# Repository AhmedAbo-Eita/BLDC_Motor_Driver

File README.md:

# 3-Phase BLDC & PMSM Motor Controller (ESC)

[-blue)](https://www.st.com/en/microcontrollers-microprocessors/stm32g431rb.html)

A high-performance, compact 3-phase Field-Oriented Control (FOC) Brushless DC (BLDC) and Permanent Magnet Synchronous Motor (PMSM) driver designed for robotics, e-mobility, actuators, and industrial automation.

This repository contains the complete end-to-end design stack:
* **Hardware:** Production-ready 8-layer PCB design (KiCad 10), complete multi-sheet schematics, BOM, Gerbers, assembly files, and LTspice circuit simulations.
* **Firmware:** Embedded C project for STM32G431 utilizing hardware CORDIC/FMAC acceleration, advanced motor timers, ADCs, and industrial communication stacks.
* **Control Modeling:** MATLAB/Simulink system-level simulation models for FOC algorithm development, parameter tuning, and sensorless state estimation.

---

## Hardware Preview (BLDC_MC_V1.0)

---

## Hardware V1.0 Summary & Highlight

### Key Technical Specifications

| Parameter | Specification | Details / Subsystem |
| :--- | :--- | :--- |
| **Operating Voltage ($V_{BUS}$)** | **24 V – 60 V** (60 V max) | Active reverse-polarity protection + TVS transient clamping |
| **Rated Phase Current** | **30 A continuous / peak** | Low $R_{DS(on)}$ MOSFETs + 8-layer high-copper thermal dissipation |
| **PWM Switching Frequency** | Up to **100 kHz** | Driven by STM32 advanced motor control timers |
| **Microcontroller** | **STM32G431RBT6** | 170 MHz ARM Cortex-M4, FPU, CORDIC & FMAC co-processors |
| **Gate Driver IC** | **TI DRV8353HRTAR** | Smart gate driver ($1.4\,\text{A}$ source / $700\,\text{mA}$ sink), $V_{DS}$ monitor |
| **Power Inverter Stage** | 6x **Infineon BSC027N10NS5** | 100 V, $2.7\,\text{m}\Omega$, SuperSO-8 (TDSON-8) with RC snubbers |
| **Current Sensing** | 3x **$1\,\text{m}\Omega$ Shunts** | Low-side 3-shunt sensing with shielded 4-wire Kelvin routing |
| **Voltage / BEMF Sensing** | 3-Phase Resistor Dividers | Buffered with active $+1.65\,\text{V}$ virtual ground (TLV9061) |
| **Position Feedback** | Hall Sensors + Encoders | Buffered 5 V to 3.3 V Hall inputs with RC filtering |
| **Onboard Memory** | **256 Kbit SPI EEPROM** | Microchip 25LC256 for calibration parameters & PID profiles |
| **Connectivity** | **CAN / CAN-FD, USB-C, UART, I2C** | TCAN334DR transceiver + USBLC6-2SC6 ESD protection |
| **Auxiliary Power Supplies** | **12 V / 5 V / 3.3 V** | LM74700 Ideal Diode, 12V Buck, NCV4274 (5V), LDL1117 (3.3V) |
| **PCB Form Factor** | **8-Layer High-TG180 FR4** | 2 oz outer copper, controlled impedance, 1.65 mm thickness |

---

## Repository Structure

```text
BLDC_Motor_Driver/
├── Control_Modeling/       # MATLAB & Simulink models for FOC algorithm simulation
├── Firmware/               # STM32G431 embedded C firmware (STM32CubeIDE)
└── Hardware/               # Hardware designs, simulations & manufacturing files
    ├── BLDC_MC_V1.0/       # KiCad design, schematics, BOM, Gerbers & 3D renders
    └── Simulation/         # LTspice circuit simulations
```

---

## Project Development Status

| Subsystem | Milestone | Status | Details |
| :--- | :--- | :---: | :--- |
| **Hardware (V1.0)** | Schematic & PCB Layout | **Completed** | 10 modular schematic sheets, DRC passed, 8-layer stackup |
| **Hardware (V1.0)** | Fabrication Files (Gerbers/BOM/PnP) | **Completed** | Full manufacturing package generated in [`Output_Job_files`](Hardware/BLDC_MC_V1.0/Output_Job_files/) |
| **Hardware (V1.0)** | Circuit Simulations | **Completed** | Hall sensor conditioning and active virtual-ground voltage sensor validated |
| **Firmware** | BSP & Low-level Drivers | **In Progress** | STM32G431 peripheral configuration (PWM timers, ADCs, SPI, CAN, UART) |
| **Firmware** | FOC & Commutation Algorithms | **In Progress** | Space Vector PWM (SVPWM), Park/Clarke transforms, current control loop |
| **Control Modeling** | System-Level Simulation | **In Progress** | Simulink motor and inverter models for tuning PI loops & observing dynamics |

---

## Detailed Hardware Documentation & Deliverables

For full details on the schematic sheet breakdown, connector pinouts, controlled impedance layout rules, and fabrication deliverables, refer to:
* **[Hardware V1.0 Comprehensive Documentation](Hardware/BLDC_MC_V1.0/Readme.md)**
* **[Hardware Versions & Overview](Hardware/Readme.md)**
* **[Schematic PDF](Hardware/BLDC_MC_V1.0/Output_Job_files/Board_SCH/BLDC_MC_V1.0.pdf)**
* **[Bill of Materials (BOM)](Hardware/BLDC_MC_V1.0/Output_Job_files/BOM_File/BLDC_MC_V1.0_PDF.pdf)**
* **[Fabrication Gerber Files](Hardware/BLDC_MC_V1.0/Output_Job_files/Fabrication_Files/)**

---

## Author & Project Information

* **Lead Hardware Engineer:** Ahmed Aboeita
* **Design Tools:** KiCad 10.0.5, STM32CubeIDE, MATLAB / Simulink, LTspice

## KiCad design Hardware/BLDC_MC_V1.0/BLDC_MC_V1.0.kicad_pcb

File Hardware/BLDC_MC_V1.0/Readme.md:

# 60V / 30A High-Performance BLDC & PMSM Motor Controller (ESC)

A compact, high-efficiency, 3-phase Field-Oriented Control (FOC) motor controller designed for high-power robotics, e-mobility, and industrial automation. Built on the **STM32G431RBT6** ARM Cortex-M4 MCU and the **TI DRV8353HRTAR** smart gate driver, this board supports high-frequency switching up to 100 kHz with extensive hardware protection, sensor feedback, and connectivity.

---

## Technical Specifications

| Parameter | Specification | Notes / Details |
| :--- | :--- | :--- |
| **Input DC Bus Voltage ($V_{BUS}$)** | **24V – 60V** (**60V Maximum**) | High-voltage bulk capacitor bank + TVS clamping |
| **Maximum Phase Current** | **30A Maximum** | Dependent on external heatsinking and thermal interface |
| **Maximum Switching Frequency** | Up to **100 kHz PWM** | Hardware-accelerated CORDIC/FMAC trigonometric engine |
| **Operating Temperature ($T_A$)** | **$-40^\circ\text{C}$ to $+125^\circ\text{C}$** | Designed for High-TG180 PCB substrates |
| **Main Processing Unit** | **STM32G431RBT6** (170 MHz) | ARM Cortex-M4 with FPU, 128KB Flash, 32KB SRAM |
| **Gate Driver IC** | **TI DRV8353HRTAR** | Smart Gate Drive ($1.4\text{A}$ source / $700\text{mA}$ sink) |
| **Power MOSFETs** | 6x **Infineon BSC027N10NS5** | 100V, $2.7\text{ m}\Omega$, SuperSO-8 (TDSON-8) |
| **Current Sense Shunts** | 3x **$1\text{ m}\Omega$ Metal Plate** | Low-side 3-shunt topology with Kelvin Sensing |
| **PCB Form Factor / Layers** | **8-Layer High-TG180 FR4** | 2 oz outer copper / 1 oz inner planes |

---

## Key Hardware Features

### 1. Processing & Control Core
* **STM32G431RBT6 MCU:** High-performance motor control MCU with integrated CORDIC co-processor for near-zero latency Park/Clarke transformations.
* **Dual Clock Source:** 24 MHz primary oscillator (`Y1`) for the main system PLL and 32.768 kHz crystal (`Y2`) for precise real-time timing.
* **Onboard Memory:** 256 Kbit SPI EEPROM (**25LC256-E/SN**) for non-volatile calibration parameters, PID coefficients, and motor profiles.

### 2. Inverter Power Stage & Gate Drive
* **Smart Gate Driver (DRV8353H):** Eliminates external gate resistors via software-tunable `IDRIVE` configuration. Features integrated $V_{DS}$ monitoring for cross-conduction and shoot-through protection.
* **Optimized Power Stage:** Low $R_{DS(on)}$ ($2.7\text{ m}\Omega$) 100V OptiMOS 5 MOSFETs paired with localized **1 nF + 4.7 $\Omega$ switch-node RC snubbers** to eliminate high-frequency parasitic ringing.
* **DC-Link Decoupling:** Low-ESR parallel ceramic capacitor bank ($4\times 47\,\mu\text{F} + 2\times 100\text{ nF}$) placed immediately across the inverter bridge for fast switching transient absorption.

### 3. Sensing & Signal Conditioning
* **3-Phase Low-Side Current Sensing:** $1\text{ m}\Omega$ shunts routed via strict 4-wire Kelvin differential pairs directly into the DRV8353 current sense amplifiers.
* **Phase Voltage / Sensorless BEMF Sensing:** Three buffered resistor divider networks ($100\text{ k}\Omega / 2.7\text{ k}\Omega$) with an active **+1.65V Virtual Ground buffer (TLV9061)** to allow full bidirectional phase voltage sampling across the MCU's ADC dynamic range.
* **Sensored Hall Interface:** Isolated Hall-effect inputs with hardware low-pass filtering and **TLV9061** op-amp buffers shifting 5V Hall signals safely to 3.125V/3.3V logic levels.

### 4. Auxiliary Power Architecture
* **Active Reverse Polarity Protection:** High-side Ideal Diode controller (**TI LM74700-Q1**) driving a power MOSFET to block reverse connection with zero diode forward-voltage drops.
* **Step-Down Buck Converter:** Converts high-voltage DC input down to an intermediate **+12V rail** for gate drive supplies.
* **Dual Linear Regulators (LDOs):**
  * **NCV4274 (5.0V):** Powers external Hall sensors and peripheral pull-ups.
  * **LDL1117S33R (3.3V):** Ultra-clean, low-noise supply for the STM32G4 MCU, analog references, and transceivers.

### 5. Robust Industrial Connectivity & Protection
* **CAN / CAN-FD Bus:** High-speed **TCAN334DR** transceiver with an **ACT1210** common-mode choke, split $60\Omega$ termination, and dedicated **PESD2CANFD24V-QCZ** ESD diode protection.
* **USB Type-C Interface:** USB 2.0 Type-C port with **USBLC6-2SC6** high-speed TVS diode array for diagnostics, firmware flashing, and PC telemetry.
* **Series Damping Resistors:** $33\,\Omega$ series termination resistors placed on all high-speed digital lines (PWM, SPI, SWD, UART, I2C) to ensure signal integrity and eliminate trace reflections.

---

## Schematic Sheet Architecture

The schematic is organized into 10 modular hierarchical sheets:

| Sheet ID | Sheet Name | Description & Subsystems |
| :---: | :--- | :--- |
| **01/10** | `BLDC_MC.kicad_sch` | Top-level hierarchical block interconnections and system bus mapping. |
| **02/10** | `BLDC_MC_V1.0_Power.kicad_sch` | LM74700 Ideal Diode, 12V Buck regulator, 5V/3.3V LDOs, status LEDs. |
| **03/10** | `BLDC_MC_V1.0_MCU.kicad_sch` | STM32G431RBT6, decoupling network, SWD debug port, USB-C interface. |
| **04/10** | `BLDC_MC_V1.0_Gate_Drive.kicad_sch` | DRV8353HRTAR smart gate driver, IDRIVE, VDS, and shunt amplifier tuning. |
| **05/10** | `BLDC_MC_V1.0_3Phase_Inverter_legs.kicad_sch` | 3-Phase MOSFET half-bridges, RC snubbers, $1\text{ m}\Omega$ current shunts. |
| **06/10** | `BLDC_MC_V1.0_HallSensor.kicad_sch` | 3-Channel Hall-effect sensor level-shifter and TLV9061 buffer circuitry. |
| **07/10** | `BLDC_MC_V1.0_Voltage_Sensor.kicad_sch` | 3-Phase BEMF divider network and +1.65V active virtual ground op-amp. |
| **08/10** | `BLDC_MC_V1.0_Memory.kicad_sch` | 25LC256 256Kbit SPI EEPROM and line termination resistors. |
| **09/10** | `BLDC_MC_V1.0_CAN_Transceiver.kicad_sch` | TCAN334DR CAN/CAN-FD transceiver, split termination, common-mode filter. |
| **10/10** | `BLDC_MC_V1.0_Connectors.kicad_sch` | High-current power pads, J8 comms header, J5 Hall header, TVS arrays. |

---

## Connector Pinout Definitions

### 1. Main Power & Motor Terminals (High Current)
* **`J6 / J9`:** DC Bus Input Power (`Vin_DC` [+] and `PGND` [-]).
* **`J1`:** Motor Phase A Output (`Phase_A`).
* **`J2`:** Motor Phase B Output (`Phase_B`).
* **`J7`:** Motor Phase C Output (`Phase_C`).

### 2. Communication Header (`J8` - 10-Pin S10B-PHDSS)
| Pin # | Net Name | Type | Description |
| :---: | :--- | :---: | :--- |
| **1** | `+3.3V` | Power | 3.3V Auxiliary Output Rail |
| **2** | `CAN_N` | Diff I/O | CAN Bus Dominant Low Line |
| **3** | `CAN_P` | Diff I/O | CAN Bus Dominant High Line |
| **4** | `I2C3_SCL` | Bidirectional | I2C Clock (STM32 Pin 40 / PC8) |
| **5** | `GND` | Ground | System Ground Return |
| **6** | `+5V` | Power | 5.0V Auxiliary Output Rail |
| **7** | `UART4_RX` | Input | UART4 Receive Line (STM32 Pin 53 / PC11) |
| **8** | `UART4_TX` | Output | UART4 Transmit Line (STM32 Pin 52 / PC10) |
| **9** | `I2C3_SDA` | Bidirectional | I2C Data (STM32 Pin 41 / PC9) |
| **10** | `GND` | Ground | System Ground Return |

### 3. Hall Sensor Header (`J5` - 6-Pin S6B-PH-K-S)
| Pin # | Net Name | Type | Description |
| :---: | :--- | :---: | :--- |
| **1** | `+5V` | Power | Hall Sensor Power Supply (5V) |
| **2** | `Hall_A` | Input | Phase A Hall Sensor Signal |
| **3** | `Hall_B` | Input | Phase B Hall Sensor Signal |
| **4** | `Hall_C` | Input | Phase C Hall Sensor Signal |
| **5** | `+3.3V` | Power | Optional 3.3V Pull-up / Supply |
| **6** | `GND` | Ground | Sensor Ground Return |

### 4. Debug & Programming (`J4` - 6-Pin SWD Header)
* **Pin 1:** `+3.3V` | **Pin 2:** `NRST` | **Pin 3:** `SWDIO` (PA13) | **Pin 4:** `SWCLK` (PA14) | **Pin 5:** `SWO` (PB3) | **Pin 6:** `GND`

---

## Recommended PCB Stackup & Layout Rules

### PCB Stackup

The board uses an 8-layer high-TG180 FR4 stackup with 1.65 mm nominal finished thickness. Copper thicknesses and dielectric spacing are nominal values from the fabrication stackup.

| Layer / Dielectric | Material | Thickness |
| :--- | :--- | :---: |
| L1 | Outer copper, 1 oz | 0.035 mm (1.38 mil) |
| L1-L2 | 2116 prepreg, RC54%, 4.9 mil | 0.094 mm (3.70 mil) |
| L2 | Inner copper | 0.030 mm (1.18 mil) |
| L2-L3 | FR4 core, 0.25 mm / 1 oz without copper | 0.250 mm (9.84 mil) |
| L3 | Inner copper | 0.030 mm (1.18 mil) |
| L3-L4 | 2116 prepreg, RC54%, 4.9 mil, 2 plies | 0.188 mm (7.40 mil) |
| L4 | Inner copper | 0.030 mm (1.18 mil) |
| L4-L5 | FR4 core, 0.25 mm / 1 oz without copper | 0.250 mm (9.84 mil) |
| L5 | Inner copper | 0.030 mm (1.18 mil) |
| L5-L6 | 2116 prepreg, RC54%, 4.9 mil, 2 plies | 0.188 mm (7.40 mil) |
| L6 | Inner copper | 0.030 mm (1.18 mil) |
| L6-L7 | FR4 core, 0.25 mm / 1 oz without copper | 0.250 mm (9.84 mil) |
| L7 | Inner copper | 0.030 mm (1.18 mil) |
| L7-L8 | 2116 prepreg, RC54%, 4.9 mil | 0.094 mm (3.70 mil) |
| L8 | Outer copper, 1 oz | 0.035 mm (1.38 mil) |

### Controlled Impedance

| Target impedance | Type | Signal layer | Reference layer | Trace width | Differential spacing |
| :---: | :--- | :---: | :---: | :---: | :---: |
| 50 ohm | Single-ended, non-coplanar | L1 | L2 | 6.790 mil (0.172 mm) | - |
| 50 ohm | Single-ended, non-coplanar | L3 | L2 / L4 | 8.370 mil (0.213 mm) | - |
| 100 ohm | Differential pair, non-coplanar | L1 | L2 | 5.270 mil (0.134 mm) | 8.000 mil (0.203 mm) |

* **Power Decoupling:** Place low-ESR ceramic caps ($47\,\mu\text{F}$) as close as physically possible to the high-side MOSFET drains and low-side source shunts.
* **Kelvin Current Sensing:** Keep `SA+`/`SA-`, `SB+`/`SB-`, and `SC+`/`SC-` routed strictly as shielded differential pairs on Layer 3, isolated from high $dv/dt$ switch-node planes.

---

## Author & Project Information
* **Lead Hardware Engineer:** Ahmed Aboeita
* **Design Suite:** KiCad E.D.A. v10.0.5
* **Design Revision:** Rev 1.0 (2026-08-17)

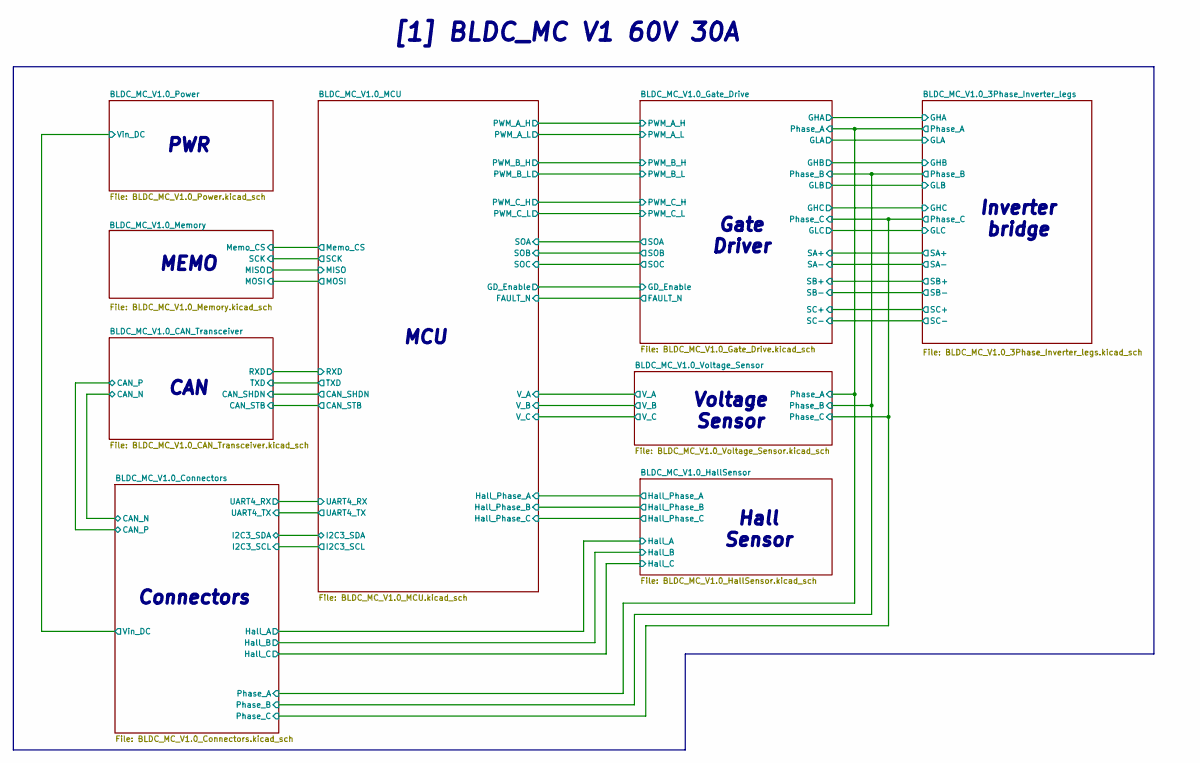
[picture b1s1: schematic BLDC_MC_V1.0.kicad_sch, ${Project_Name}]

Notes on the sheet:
Inverter bridge
MEMO
[1] BLDC_MC V1 60V 30A
Voltage Sensor
CAN
Gate Driver
Hall Sensor
Connectors
PWR
MCU

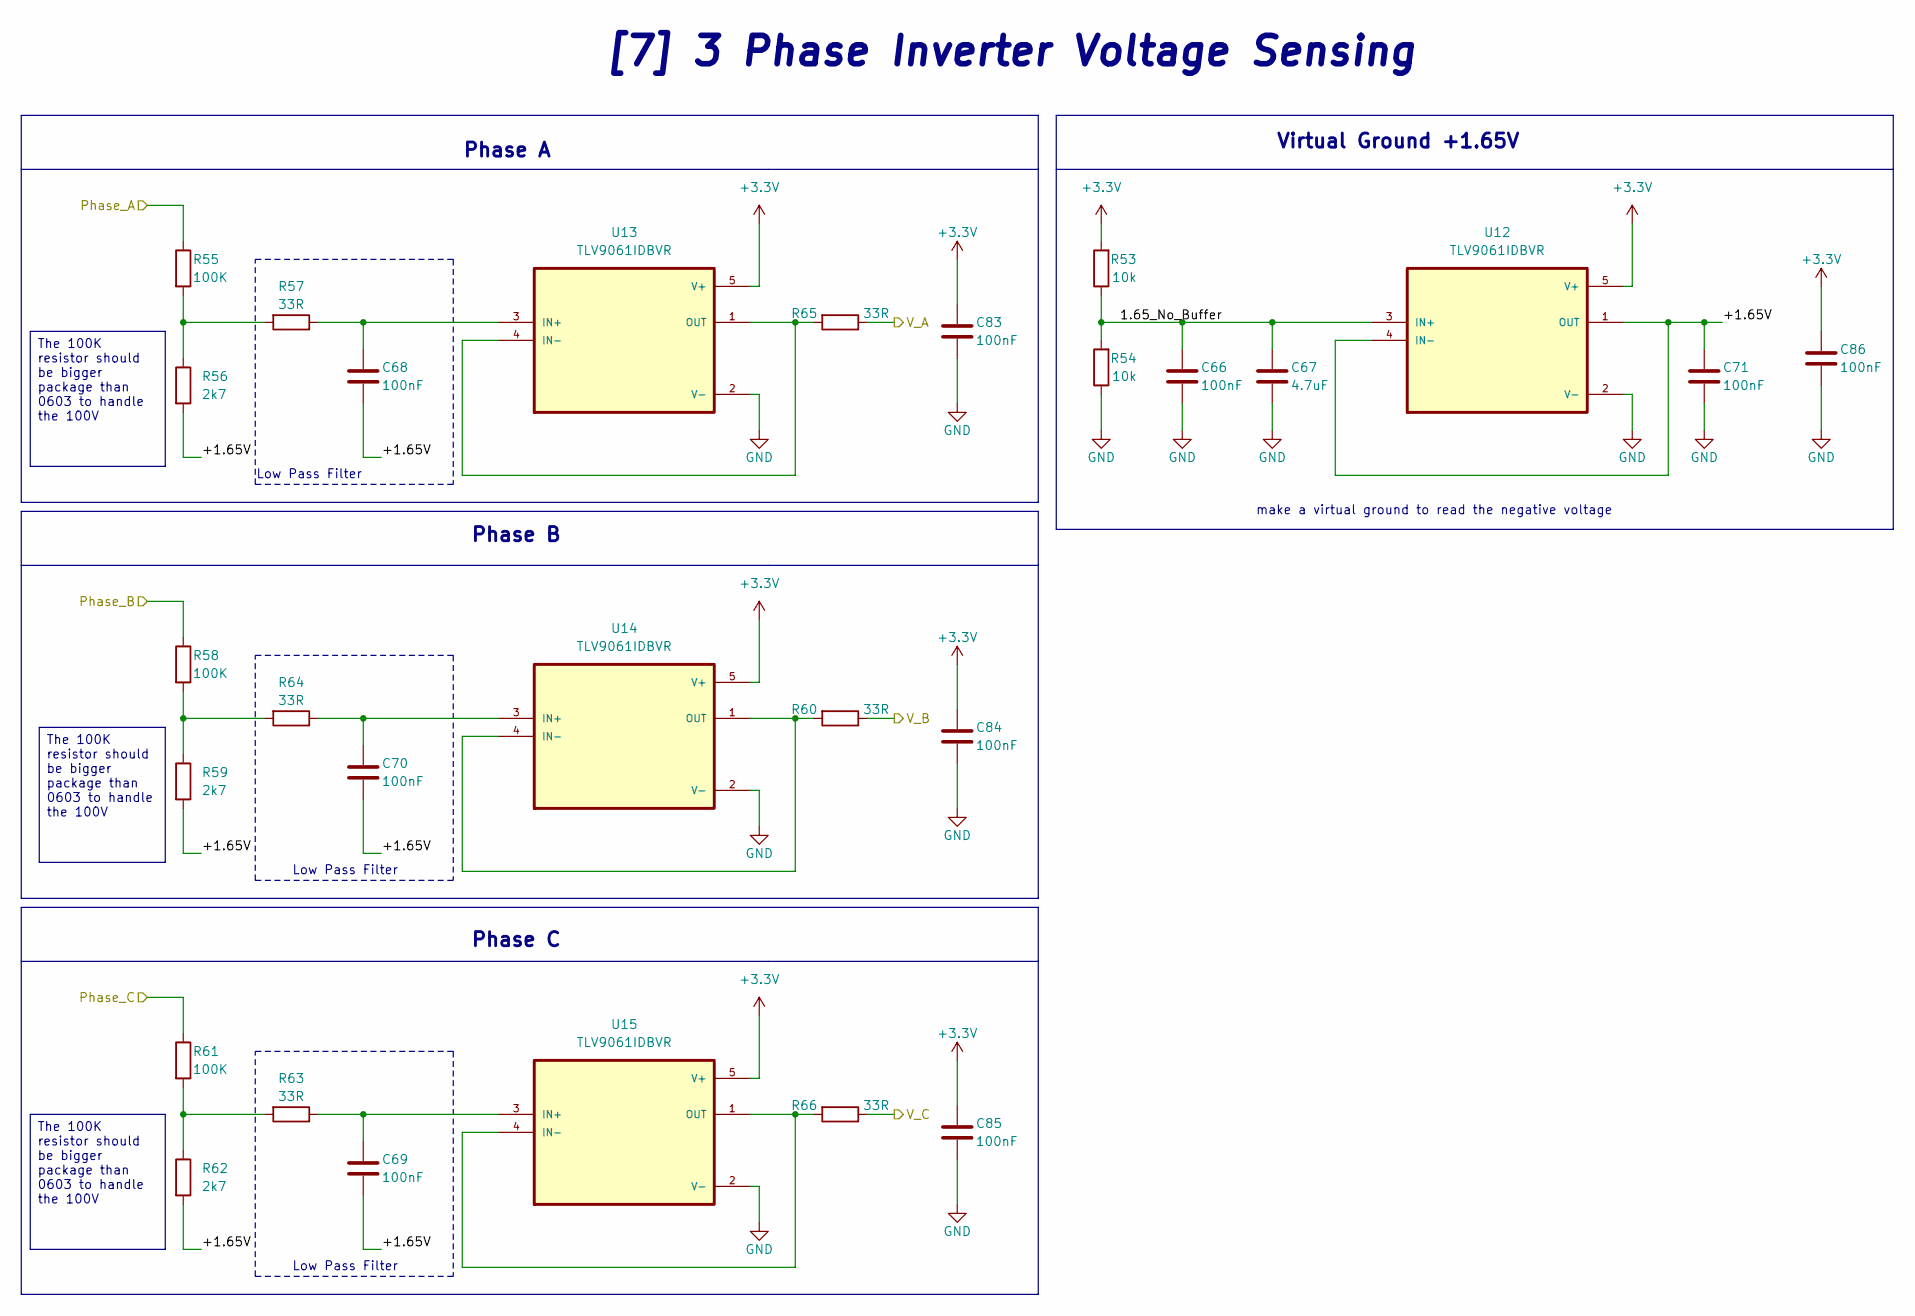
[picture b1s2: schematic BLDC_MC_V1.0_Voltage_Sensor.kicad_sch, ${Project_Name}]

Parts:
C66, C68, C69, C70, C71, C83, C84, C85, C86: 100nF; C_0805_2012Metric; LCSC_PN C28233
C67: 4.7uF; C_1206_3216Metric; LCSC_PN C51205
R53, R54: 10k; R_0603_1608Metric; LCSC_PN C95204
R55, R58, R61: 100K; R_1206_3216Metric; LCSC_PN C2907368
R56, R59, R62: 2k7; R_0603_1608Metric; LCSC_PN C705760
R57, R60, R63, R64, R65, R66: 33R; R_0603_1608Metric; LCSC_PN C108661
U12, U13, U14, U15: TLV9061IDBVR; SOT95P280X145-5N; LCSC_PN C398358

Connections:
+3.3V: C83.1, C84.1, C85.1, C86.1, R53.2, U12.5 (V+), U13.5 (V+), U14.5 (V+), U15.5 (V+); also elsewhere on the board
/BLDC_MC_V1.0_3Phase_Inverter_legs/Phase_A: R55.1; also elsewhere on the board
/BLDC_MC_V1.0_3Phase_Inverter_legs/Phase_B: R58.1; also elsewhere on the board
/BLDC_MC_V1.0_3Phase_Inverter_legs/Phase_C: R61.1; also elsewhere on the board
/BLDC_MC_V1.0_MCU/V_A: R65.1; also elsewhere on the board
/BLDC_MC_V1.0_MCU/V_B: R60.1; also elsewhere on the board
/BLDC_MC_V1.0_MCU/V_C: R66.1; also elsewhere on the board
/BLDC_MC_V1.0_Voltage_Sensor/1.65_No_Buffer: C66.1, C67.1, R53.1, R54.2, U12.3 (IN+)
/BLDC_MC_V1.0_Voltage_Sensor/+1.65V: C68.2, C69.2, C70.2, C71.1, R56.2, R59.2, R62.2, U12.1 (OUT), U12.4 (IN-)
GND: C66.2, C67.2, C71.2, C83.2, C84.2, C85.2, C86.2, R54.1, U12.2 (V-), U13.2 (V-), U14.2 (V-), U15.2 (V-); also elsewhere on the board
unnamed: R55.2, R56.1, R57.2
unnamed: R58.2, R59.1, R64.2
unnamed: R61.2, R62.1, R63.2
unnamed: C68.1, R57.1, U13.3 (IN+)
unnamed: R65.2, U13.1 (OUT), U13.4 (IN-)
unnamed: C70.1, R64.1, U14.3 (IN+)
unnamed: R60.2, U14.1 (OUT), U14.4 (IN-)
unnamed: C69.1, R63.1, U15.3 (IN+)
unnamed: R66.2, U15.1 (OUT), U15.4 (IN-)

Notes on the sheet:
Phase B
make a virtual ground to read the negative voltage
Virtual Ground +1.65V
Low Pass Filter
Phase C
Phase A
[7] 3 Phase Inverter Voltage Sensing
The 100K resistor should be bigger package than 0603 to handle the 100V

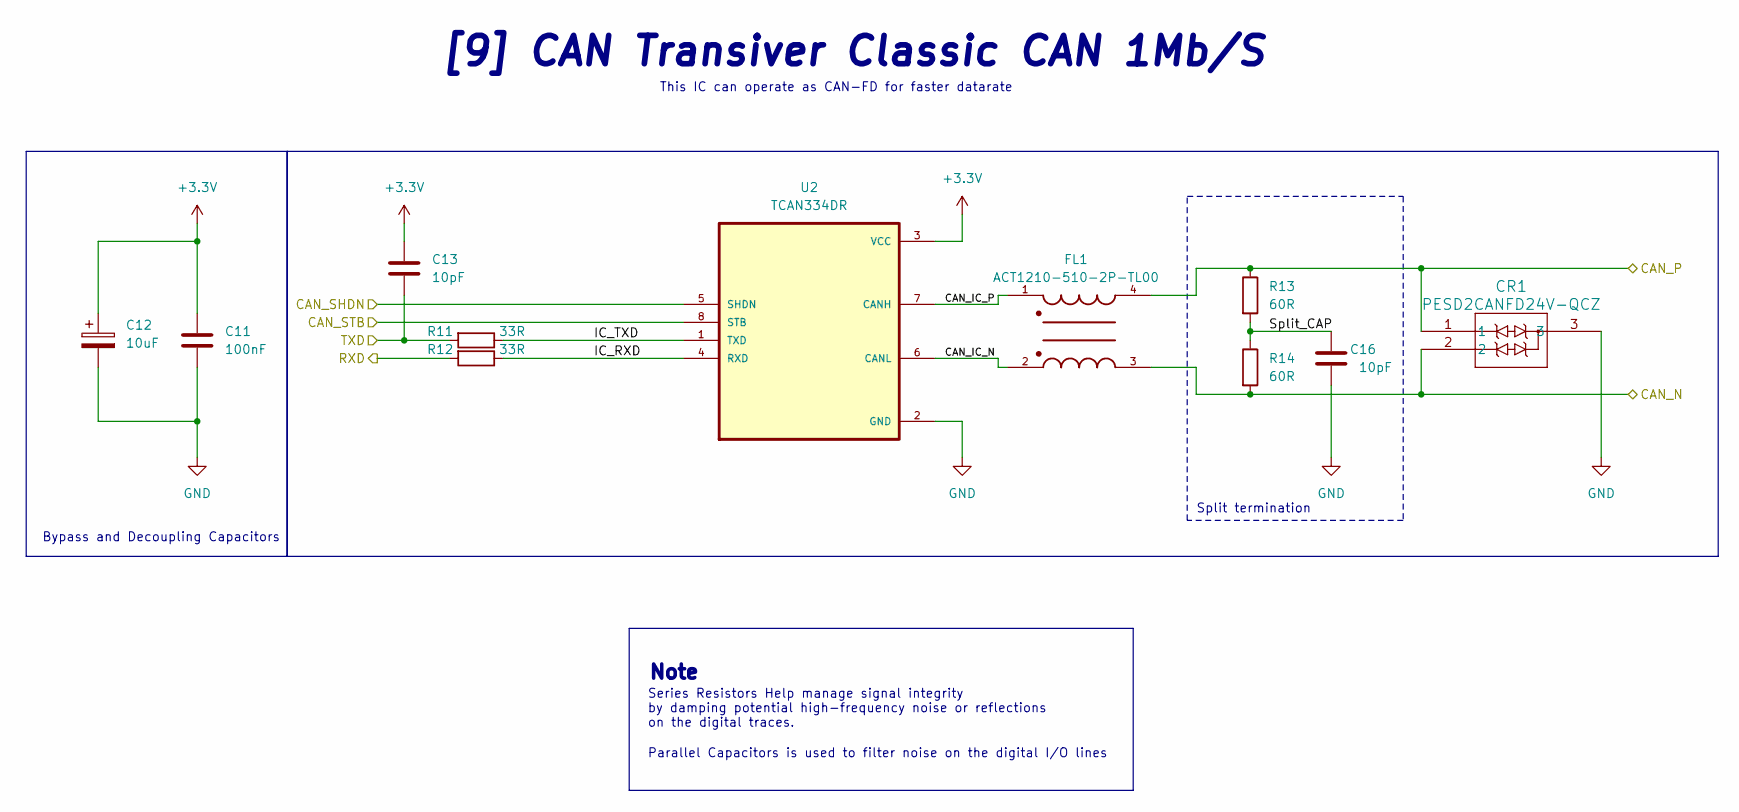
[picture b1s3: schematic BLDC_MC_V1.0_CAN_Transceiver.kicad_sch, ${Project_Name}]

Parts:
C11: 100nF; C_0805_2012Metric; LCSC_PN C28233
C12: 10uF; CP_EIA-3216-18_Kemet-A; LCSC_PN C7171
C13, C16: 10pF; C_0603_1608Metric; LCSC_PN C1634
CR1: PESD2CANFD24V-QCZ; DFN1412D-3_SOT8009_NEX; LCSC_PN C6251381
FL1: ACT1210-510-2P-TL00; FIL_ACT1210-510-2P-TL00; PARTREV 5/31/2021; LCSC_PN C95572
R11, R12: 33R; R_0603_1608Metric; LCSC_PN C108661
R13, R14: 60R; C_0603_1608Metric; LCSC_PN C166918
U2: TCAN334DR; SOIC127P599X175-8N

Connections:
+3.3V: C11.1, C12.1, C13.1, U2.3 (VCC); also elsewhere on the board
/BLDC_MC_V1.0_CAN_Transceiver/CAN_IC_N: FL1.2, U2.6 (CANL)
/BLDC_MC_V1.0_CAN_Transceiver/CAN_IC_P: FL1.1, U2.7 (CANH)
/BLDC_MC_V1.0_CAN_Transceiver/CAN_N: CR1.2, FL1.3, R14.2; also elsewhere on the board
/BLDC_MC_V1.0_CAN_Transceiver/CAN_P: CR1.1, FL1.4, R13.1; also elsewhere on the board
/BLDC_MC_V1.0_CAN_Transceiver/CAN_SHDN: U2.5 (SHDN); also elsewhere on the board
/BLDC_MC_V1.0_CAN_Transceiver/CAN_STB: U2.8 (STB); also elsewhere on the board
/BLDC_MC_V1.0_CAN_Transceiver/IC_RXD: R12.1, U2.4 (RXD)
/BLDC_MC_V1.0_CAN_Transceiver/IC_TXD: R11.1, U2.1 (TXD)
/BLDC_MC_V1.0_CAN_Transceiver/RXD: R12.2; also elsewhere on the board
/BLDC_MC_V1.0_CAN_Transceiver/Split_CAP: C16.1, R13.2, R14.1
/BLDC_MC_V1.0_CAN_Transceiver/TXD: C13.2, R11.2; also elsewhere on the board
GND: C11.2, C12.2, C16.2, CR1.3, U2.2 (GND); also elsewhere on the board

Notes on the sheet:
Series Resistors Help manage signal integrity by damping potential high-frequency noise or reflections on the digital traces.
Parallel Capacitors is used to filter noise on the digital I/O lines
Bypass and Decoupling Capacitors
[9] CAN Transiver Classic CAN 1Mb/S
Split termination
Note
This IC can operate as CAN-FD for faster datarate

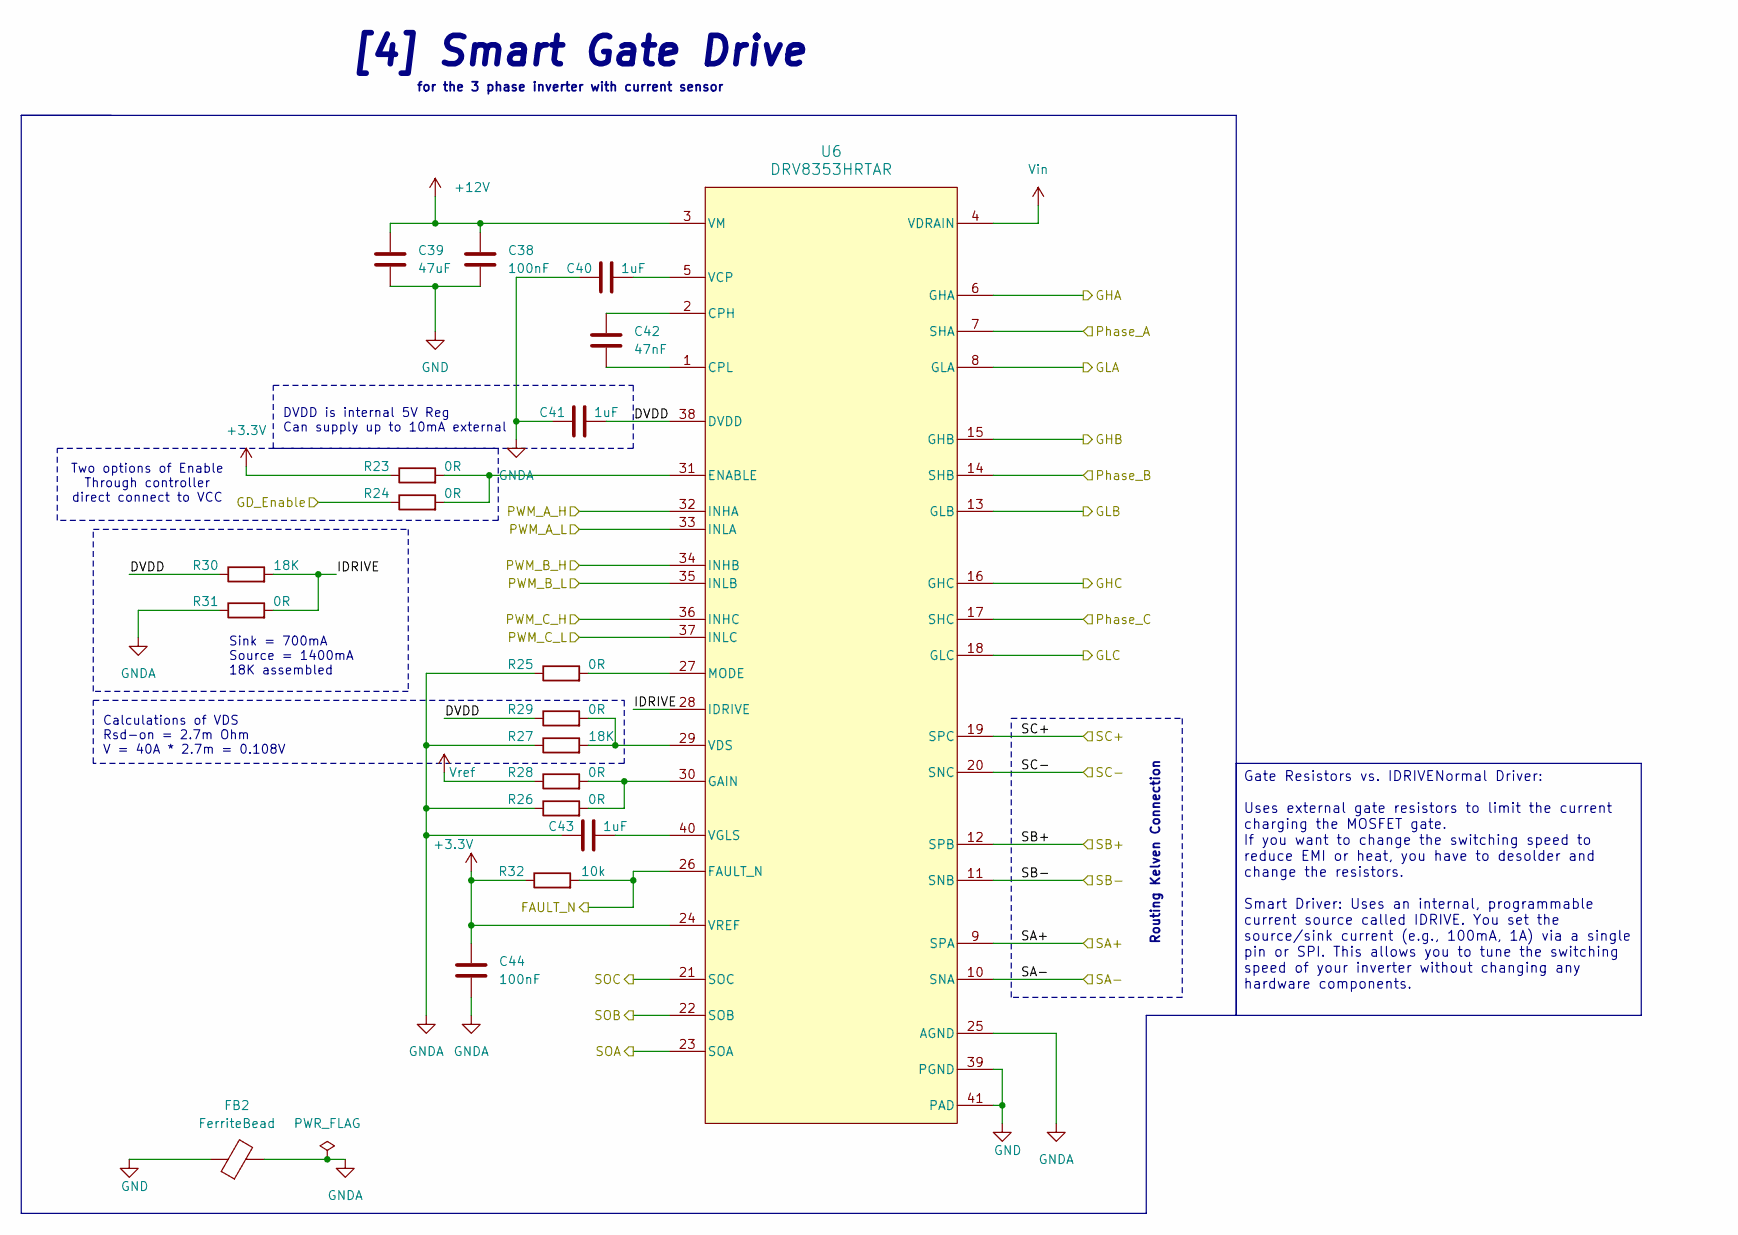
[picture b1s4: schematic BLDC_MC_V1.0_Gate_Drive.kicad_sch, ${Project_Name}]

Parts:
C38, C44: 100nF; C_0805_2012Metric; LCSC_PN C28233
C39: 47uF; C_1206_3216Metric; LCSC_PN C403725
C40, C41, C43: 1uF; C_0603_1608Metric; LCSC_PN C29936
C42: 47nF; C_0603_1608Metric; LCSC_PN C1622
FB2: FerriteBead; L_0603_1608Metric; LCSC_PN C19330
R23, R24, R25, R26, R28, R29, R31: 0R; R_0603_1608Metric; LCSC_PN C2906974
R27, R30: 18K; R_0603_1608Metric; LCSC_PN C309650
R32: 10k; R_0603_1608Metric; LCSC_PN C98220
U6: DRV8353HRTAR; RTA0040B; LCSC_PN C2150766

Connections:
+3.3V: C44.1, R23.1, R32.1, U6.24 (VREF); also elsewhere on the board
+12V: C38.1, C39.2, U6.3 (VM); also elsewhere on the board
/BLDC_MC_V1.0_3Phase_Inverter_legs/GHA: U6.6 (GHA); also elsewhere on the board
/BLDC_MC_V1.0_3Phase_Inverter_legs/GHB: U6.15 (GHB); also elsewhere on the board
/BLDC_MC_V1.0_3Phase_Inverter_legs/GHC: U6.16 (GHC); also elsewhere on the board
/BLDC_MC_V1.0_3Phase_Inverter_legs/GLA: U6.8 (GLA); also elsewhere on the board
/BLDC_MC_V1.0_3Phase_Inverter_legs/GLB: U6.13 (GLB); also elsewhere on the board
/BLDC_MC_V1.0_3Phase_Inverter_legs/GLC: U6.18 (GLC); also elsewhere on the board
/BLDC_MC_V1.0_3Phase_Inverter_legs/Phase_A: U6.7 (SHA); also elsewhere on the board
/BLDC_MC_V1.0_3Phase_Inverter_legs/Phase_B: U6.14 (SHB); also elsewhere on the board
/BLDC_MC_V1.0_3Phase_Inverter_legs/Phase_C: U6.17 (SHC); also elsewhere on the board
/BLDC_MC_V1.0_Gate_Drive/DVDD: C41.2, R29.1, R30.1, U6.38 (DVDD)
/BLDC_MC_V1.0_Gate_Drive/FAULT_N: R32.2, U6.26 (FAULT_N); also elsewhere on the board
/BLDC_MC_V1.0_Gate_Drive/GD_Enable: R24.1; also elsewhere on the board
/BLDC_MC_V1.0_Gate_Drive/IDRIVE: R30.2, R31.2, U6.28 (IDRIVE)
/BLDC_MC_V1.0_Gate_Drive/PWM_A_H: U6.32 (INHA); also elsewhere on the board
/BLDC_MC_V1.0_Gate_Drive/PWM_A_L: U6.33 (INLA); also elsewhere on the board
/BLDC_MC_V1.0_Gate_Drive/PWM_B_H: U6.34 (INHB); also elsewhere on the board
/BLDC_MC_V1.0_Gate_Drive/PWM_B_L: U6.35 (INLB); also elsewhere on the board
/BLDC_MC_V1.0_Gate_Drive/PWM_C_H: U6.36 (INHC); also elsewhere on the board
/BLDC_MC_V1.0_Gate_Drive/PWM_C_L: U6.37 (INLC); also elsewhere on the board
/BLDC_MC_V1.0_Gate_Drive/SA+: U6.9 (SPA); also elsewhere on the board
/BLDC_MC_V1.0_Gate_Drive/SA-: U6.10 (SNA); also elsewhere on the board
/BLDC_MC_V1.0_Gate_Drive/SB+: U6.12 (SPB); also elsewhere on the board
/BLDC_MC_V1.0_Gate_Drive/SB-: U6.11 (SNB); also elsewhere on the board
/BLDC_MC_V1.0_Gate_Drive/SC+: U6.19 (SPC); also elsewhere on the board
/BLDC_MC_V1.0_Gate_Drive/SC-: U6.20 (SNC); also elsewhere on the board
/BLDC_MC_V1.0_Gate_Drive/SOA: U6.23 (SOA); also elsewhere on the board
/BLDC_MC_V1.0_Gate_Drive/SOB: U6.22 (SOB); also elsewhere on the board
/BLDC_MC_V1.0_Gate_Drive/SOC: U6.21 (SOC); also elsewhere on the board
GND: C38.2, C39.1, FB2.1, U6.39 (PGND), U6.41 (PAD); also elsewhere on the board
GNDA: C40.1, C41.1, C43.1, C44.2, FB2.2, R25.1, R26.1, R27.1, R31.1, U6.25 (AGND)
unnamed: C42.1, U6.2 (CPH)
unnamed: C42.2, U6.1 (CPL)
unnamed: R23.2, R24.2, U6.31 (ENABLE)
unnamed: R26.2, R28.2, U6.30 (GAIN)
unnamed: R25.2, U6.27 (MODE)
unnamed: C40.2, U6.5 (VCP)
unnamed: R27.2, R29.2, U6.29 (VDS)
unnamed: C43.2, U6.40 (VGLS)
Vin: U6.4 (VDRAIN); also elsewhere on the board
Vref: R28.1; also elsewhere on the board

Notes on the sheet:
Calculations of VDS Rsd-on = 2.7m Ohm V = 40A * 2.7m = 0.108V
Two options of Enable Through controller direct connect to VCC
[4] Smart Gate Drive
Routing Kelven Connection
for the 3 phase inverter with current sensor
DVDD is internal 5V Reg Can supply up to 10mA external
Sink = 700mA Source = 1400mA 18K assembled
Gate Resistors vs. IDRIVENormal Driver: Uses external gate resistors to limit the current charging the MOSFET gate. If you want to change the switching speed to reduce EMI or heat, you have to desolder and change the resistors. Smart Driver: Uses an internal, programmable current source called IDRI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

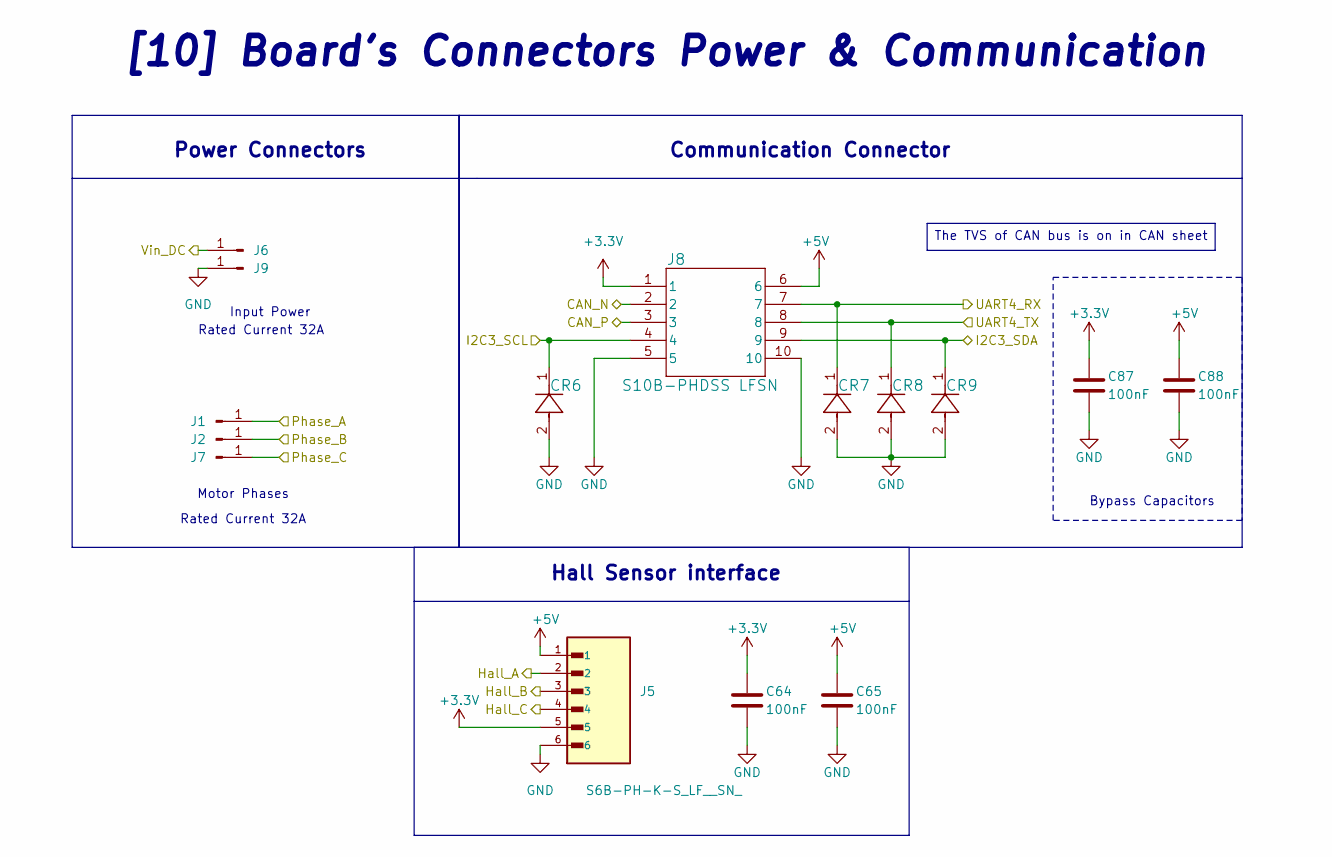
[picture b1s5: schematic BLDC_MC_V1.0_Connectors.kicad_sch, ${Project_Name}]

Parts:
C64, C65, C87, C88: 100nF; C_0805_2012Metric; LCSC_PN C28233
CR6, CR7, CR8, CR9: PESD3V3L1BA_115; DIODE_PESD3V3L1BA_115_NEX; LCSC_PN C552513
J1, J2, J6, J7, J9: Conn_01x01_Pin; PWR_CON_L
J5: S6B-PH-K-S_LF__SN_; JST_S6B-PH-K-S_LF__SN_; PARTREV R0; LCSC_PN C157920
J8: S10B-PHDSS LFSN; CONN_S10B-PHDSS_JST; LCSC_PN C161672

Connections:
+3.3V: C64.1, C87.1, J5.5, J8.1; also elsewhere on the board
+5V: C65.1, C88.1, J5.1, J8.6; also elsewhere on the board
/BLDC_MC_V1.0_3Phase_Inverter_legs/Phase_A: J1.1 (Pin_1_1); also elsewhere on the board
/BLDC_MC_V1.0_3Phase_Inverter_legs/Phase_B: J2.1 (Pin_1_1); also elsewhere on the board
/BLDC_MC_V1.0_3Phase_Inverter_legs/Phase_C: J7.1 (Pin_1_1); also elsewhere on the board
/BLDC_MC_V1.0_CAN_Transceiver/CAN_N: J8.2; also elsewhere on the board
/BLDC_MC_V1.0_CAN_Transceiver/CAN_P: J8.3; also elsewhere on the board
/BLDC_MC_V1.0_Connectors/Hall_A: J5.2; also elsewhere on the board
/BLDC_MC_V1.0_Connectors/Hall_B: J5.3; also elsewhere on the board
/BLDC_MC_V1.0_Connectors/Hall_C: J5.4; also elsewhere on the board
/BLDC_MC_V1.0_Connectors/I2C3_SCL: CR6.1, J8.4; also elsewhere on the board
/BLDC_MC_V1.0_Connectors/I2C3_SDA: CR9.1, J8.9; also elsewhere on the board
/BLDC_MC_V1.0_Connectors/UART4_RX: CR7.1, J8.7; also elsewhere on the board
/BLDC_MC_V1.0_Connectors/UART4_TX: CR8.1, J8.8; also elsewhere on the board
/BLDC_MC_V1.0_Connectors/Vin_DC: J6.1 (Pin_1_1); also elsewhere on the board
GND: C64.2, C65.2, C87.2, C88.2, CR6.2, CR7.2, CR8.2, CR9.2, J5.6, J8.5, J8.10, J9.1 (Pin_1_1); also elsewhere on the board

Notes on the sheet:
Rated Current 32A
Motor Phases
[10] Board's Connectors Power & Communication
Communication Connector
Bypass Capacitors
Hall Sensor interface
Input Power
Power Connectors
The TVS of CAN bus is on in CAN sheet

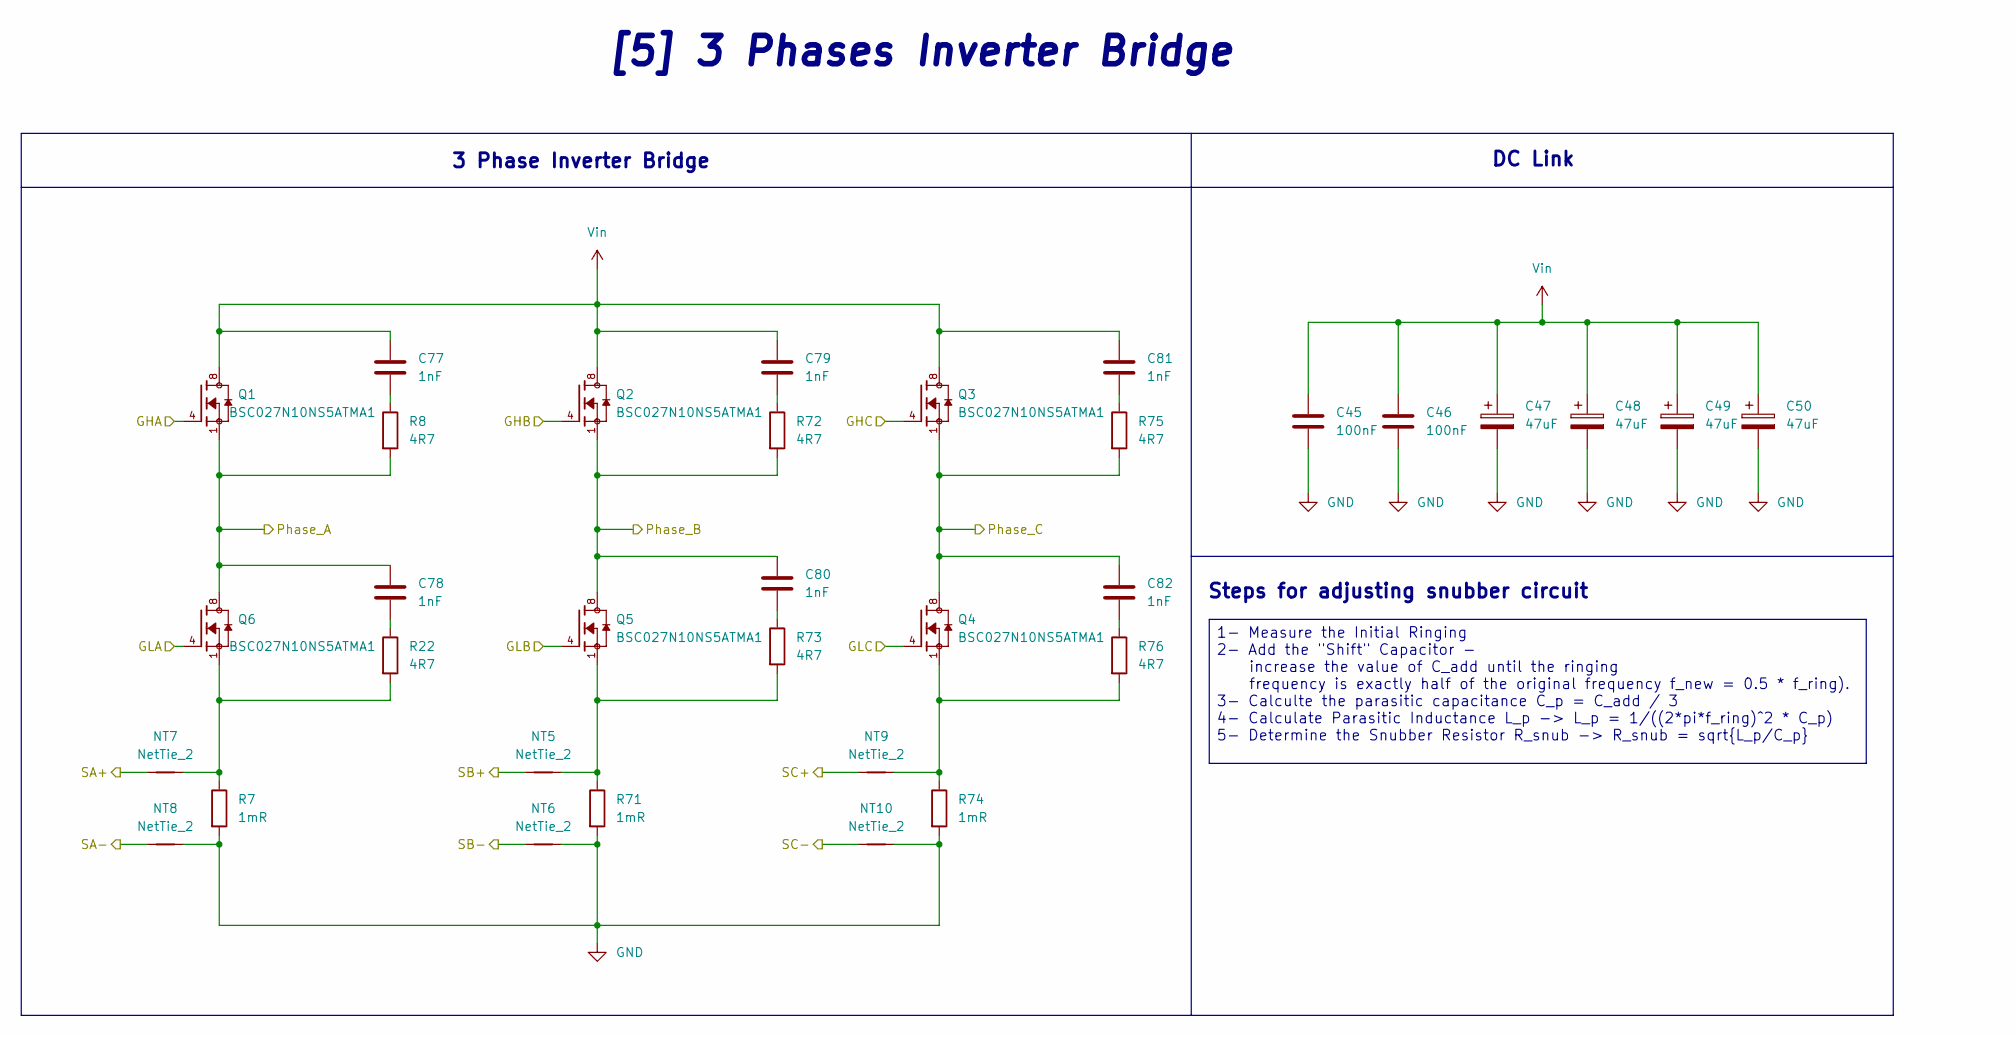
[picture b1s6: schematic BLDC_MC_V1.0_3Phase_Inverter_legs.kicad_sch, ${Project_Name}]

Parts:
C45, C46: 100nF; C_0805_2012Metric; LCSC_PN C28233
C47, C48, C49, C50: 47uF; CP_Elec_10x10.5; LCSC_PN C46528101
C77, C78, C79, C80, C81, C82: 1nF; C_1206_3216Metric; LCSC_PN C23631
NT5, NT6, NT7, NT8, NT9, NT10: NetTie_2; NetTie-2_SMD_Pad0.5mm
Q1, Q2, Q3, Q4, Q5, Q6: BSC027N10NS5ATMA1; PG-TSON-8-3_INF; PARTREV 2.1; LCSC_PN C534315
R7, R71, R74: 1mR; R_2512_6332Metric; LCSC_PN C7419999
R8, R22, R72, R73, R75, R76: 4R7; R_2512_6332Metric_Pad1.40x3.35mm_HandSolder; LCSC_PN C25489

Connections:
/BLDC_MC_V1.0_3Phase_Inverter_legs/GHA: Q1.4; also elsewhere on the board
/BLDC_MC_V1.0_3Phase_Inverter_legs/GHB: Q2.4; also elsewhere on the board
/BLDC_MC_V1.0_3Phase_Inverter_legs/GHC: Q3.4; also elsewhere on the board
/BLDC_MC_V1.0_3Phase_Inverter_legs/GLA: Q6.4; also elsewhere on the board
/BLDC_MC_V1.0_3Phase_Inverter_legs/GLB: Q5.4; also elsewhere on the board
/BLDC_MC_V1.0_3Phase_Inverter_legs/GLC: Q4.4; also elsewhere on the board
/BLDC_MC_V1.0_3Phase_Inverter_legs/Phase_A: C78.1, Q1.1, Q1.2, Q1.3, Q6.5, Q6.6, Q6.7, Q6.8, R8.2; also elsewhere on the board
/BLDC_MC_V1.0_3Phase_Inverter_legs/Phase_B: C80.1, Q2.1, Q2.2, Q2.3, Q5.5, Q5.6, Q5.7, Q5.8, R72.2; also elsewhere on the board
/BLDC_MC_V1.0_3Phase_Inverter_legs/Phase_C: C82.1, Q3.1, Q3.2, Q3.3, Q4.5, Q4.6, Q4.7, Q4.8, R75.2; also elsewhere on the board
/BLDC_MC_V1.0_Gate_Drive/SA+: NT7.1; also elsewhere on the board
/BLDC_MC_V1.0_Gate_Drive/SA-: NT8.1; also elsewhere on the board
/BLDC_MC_V1.0_Gate_Drive/SB+: NT5.1; also elsewhere on the board
/BLDC_MC_V1.0_Gate_Drive/SB-: NT6.1; also elsewhere on the board
/BLDC_MC_V1.0_Gate_Drive/SC+: NT9.1; also elsewhere on the board
/BLDC_MC_V1.0_Gate_Drive/SC-: NT10.1; also elsewhere on the board
GND: C45.2, C46.2, C47.2, C48.2, C49.2, C50.2, NT6.2, NT8.2, NT10.2, R7.2, R71.2, R74.2; also elsewhere on the board
unnamed: C77.2, R8.1
unnamed: C78.2, R22.1
unnamed: C79.2, R72.1
unnamed: C80.2, R73.1
unnamed: C81.2, R75.1
unnamed: C82.2, R76.1
unnamed: NT5.2, Q5.1, Q5.2, Q5.3, R71.1, R73.2
unnamed: NT7.2, Q6.1, Q6.2, Q6.3, R7.1, R22.2
unnamed: NT9.2, Q4.1, Q4.2, Q4.3, R74.1, R76.2
Vin: C45.1, C46.1, C47.1, C48.1, C49.1, C50.1, C77.1, C79.1, C81.1, Q1.5, Q1.6, Q1.7, Q1.8, Q2.5, Q2.6, Q2.7, Q2.8, Q3.5, Q3.6, Q3.7, Q3.8; also elsewhere on the board

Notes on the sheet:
[5] 3 Phases Inverter Bridge
3 Phase Inverter Bridge
Steps for adjusting snubber circuit
DC Link
1- Measure the Initial Ringing 2- Add the "Shift" Capacitor - increase the value of C_add until the ringing frequency is exactly half of the original frequency f_new = 0.5 * f_ring). 3- Calculte the parasitic capacitance C_p = C_add / 3 4- Calculate Parasitic Inductance L_p -> L_p = 1/((2*pi*f_ring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
